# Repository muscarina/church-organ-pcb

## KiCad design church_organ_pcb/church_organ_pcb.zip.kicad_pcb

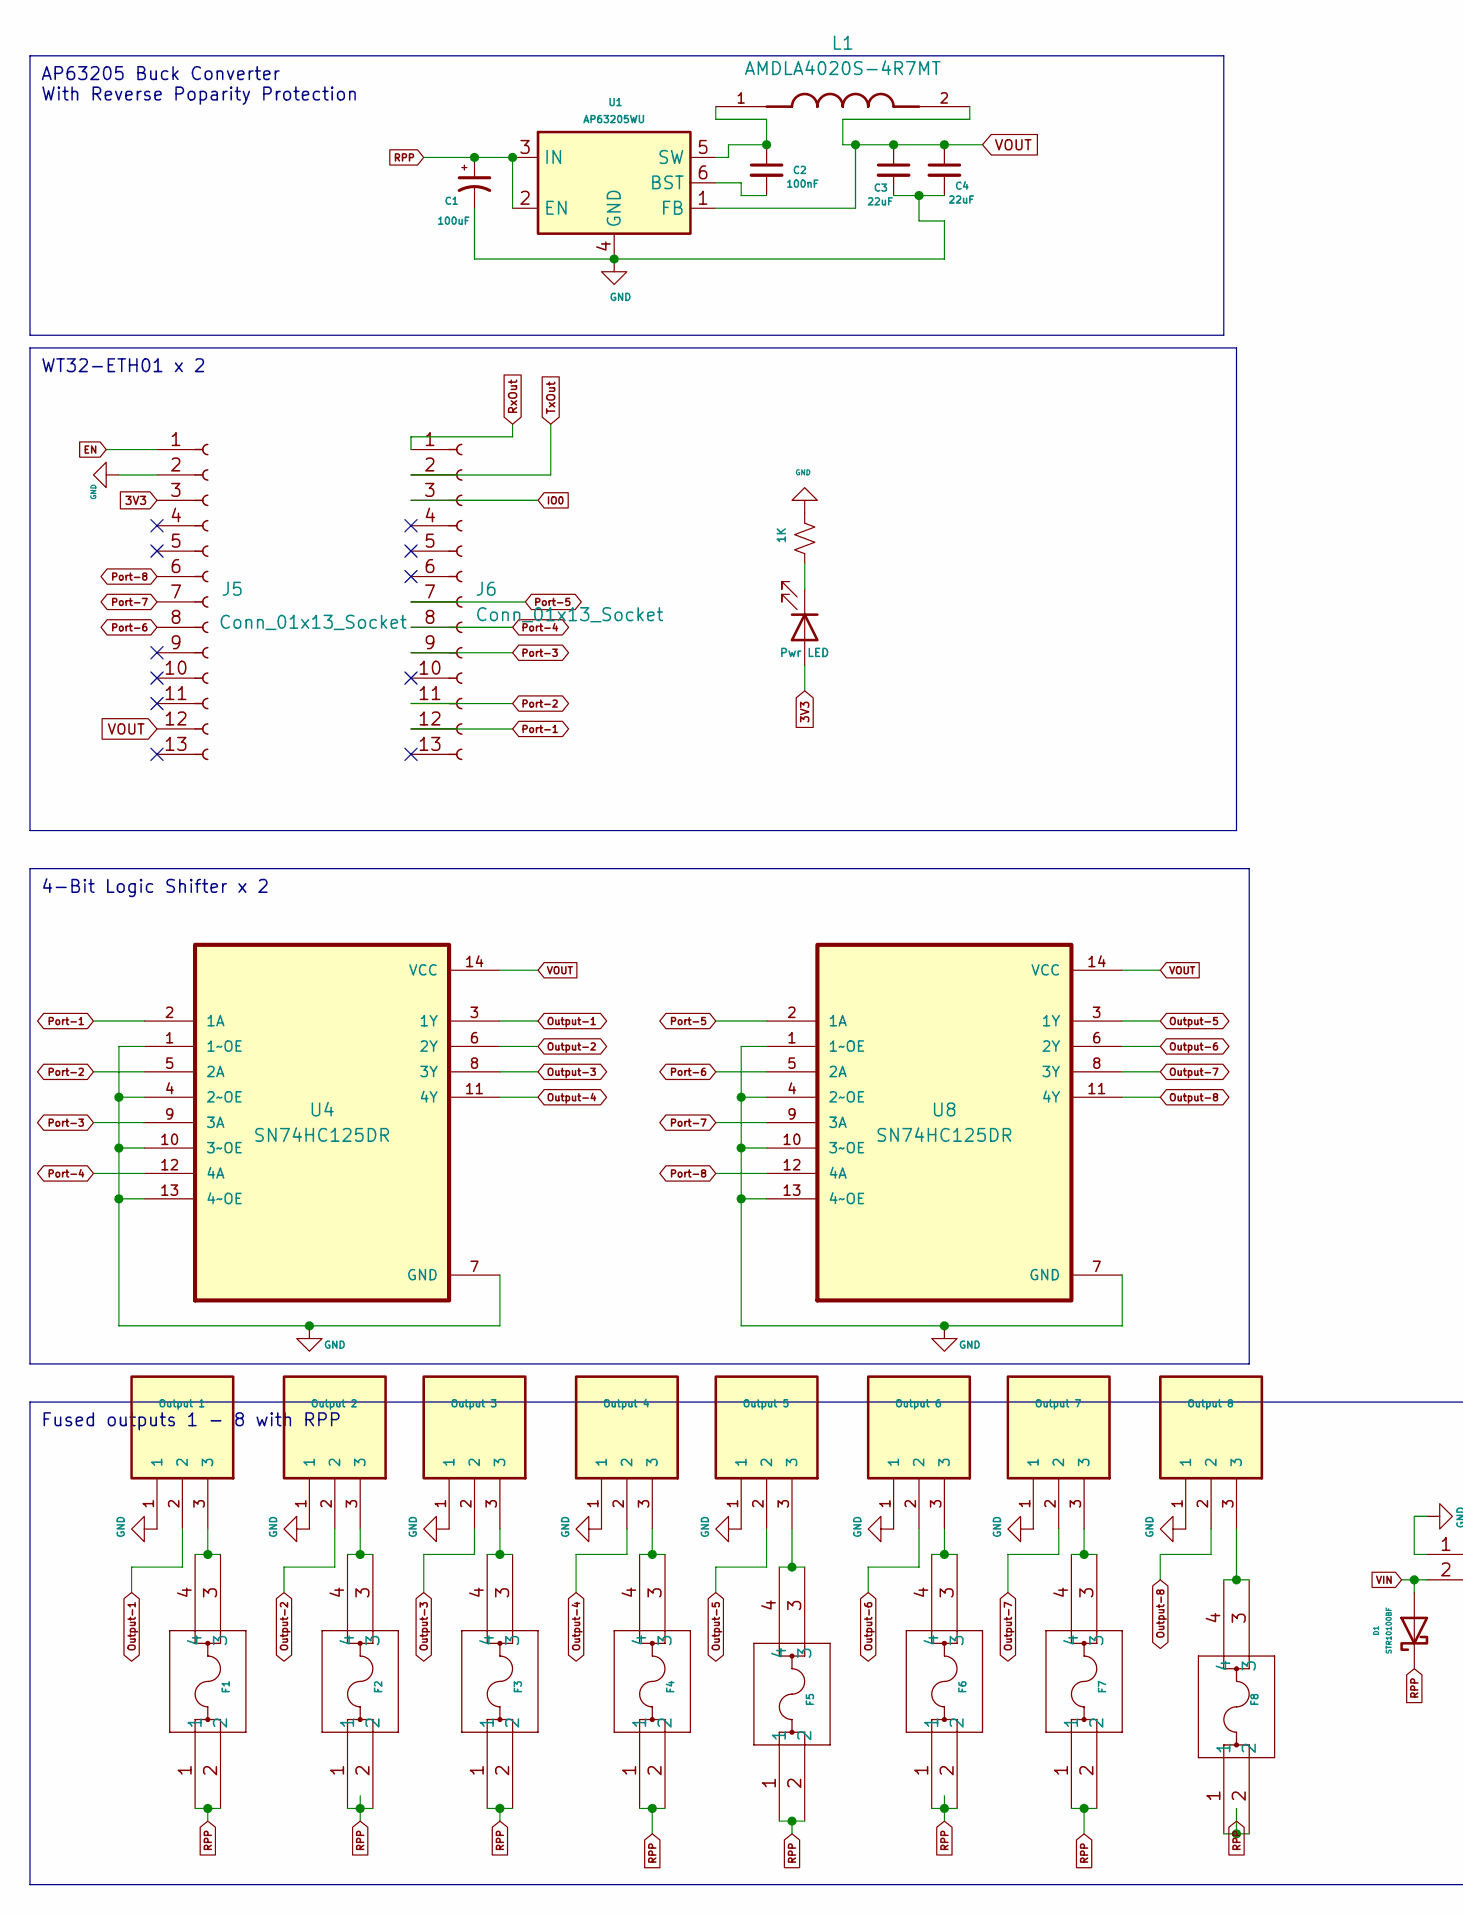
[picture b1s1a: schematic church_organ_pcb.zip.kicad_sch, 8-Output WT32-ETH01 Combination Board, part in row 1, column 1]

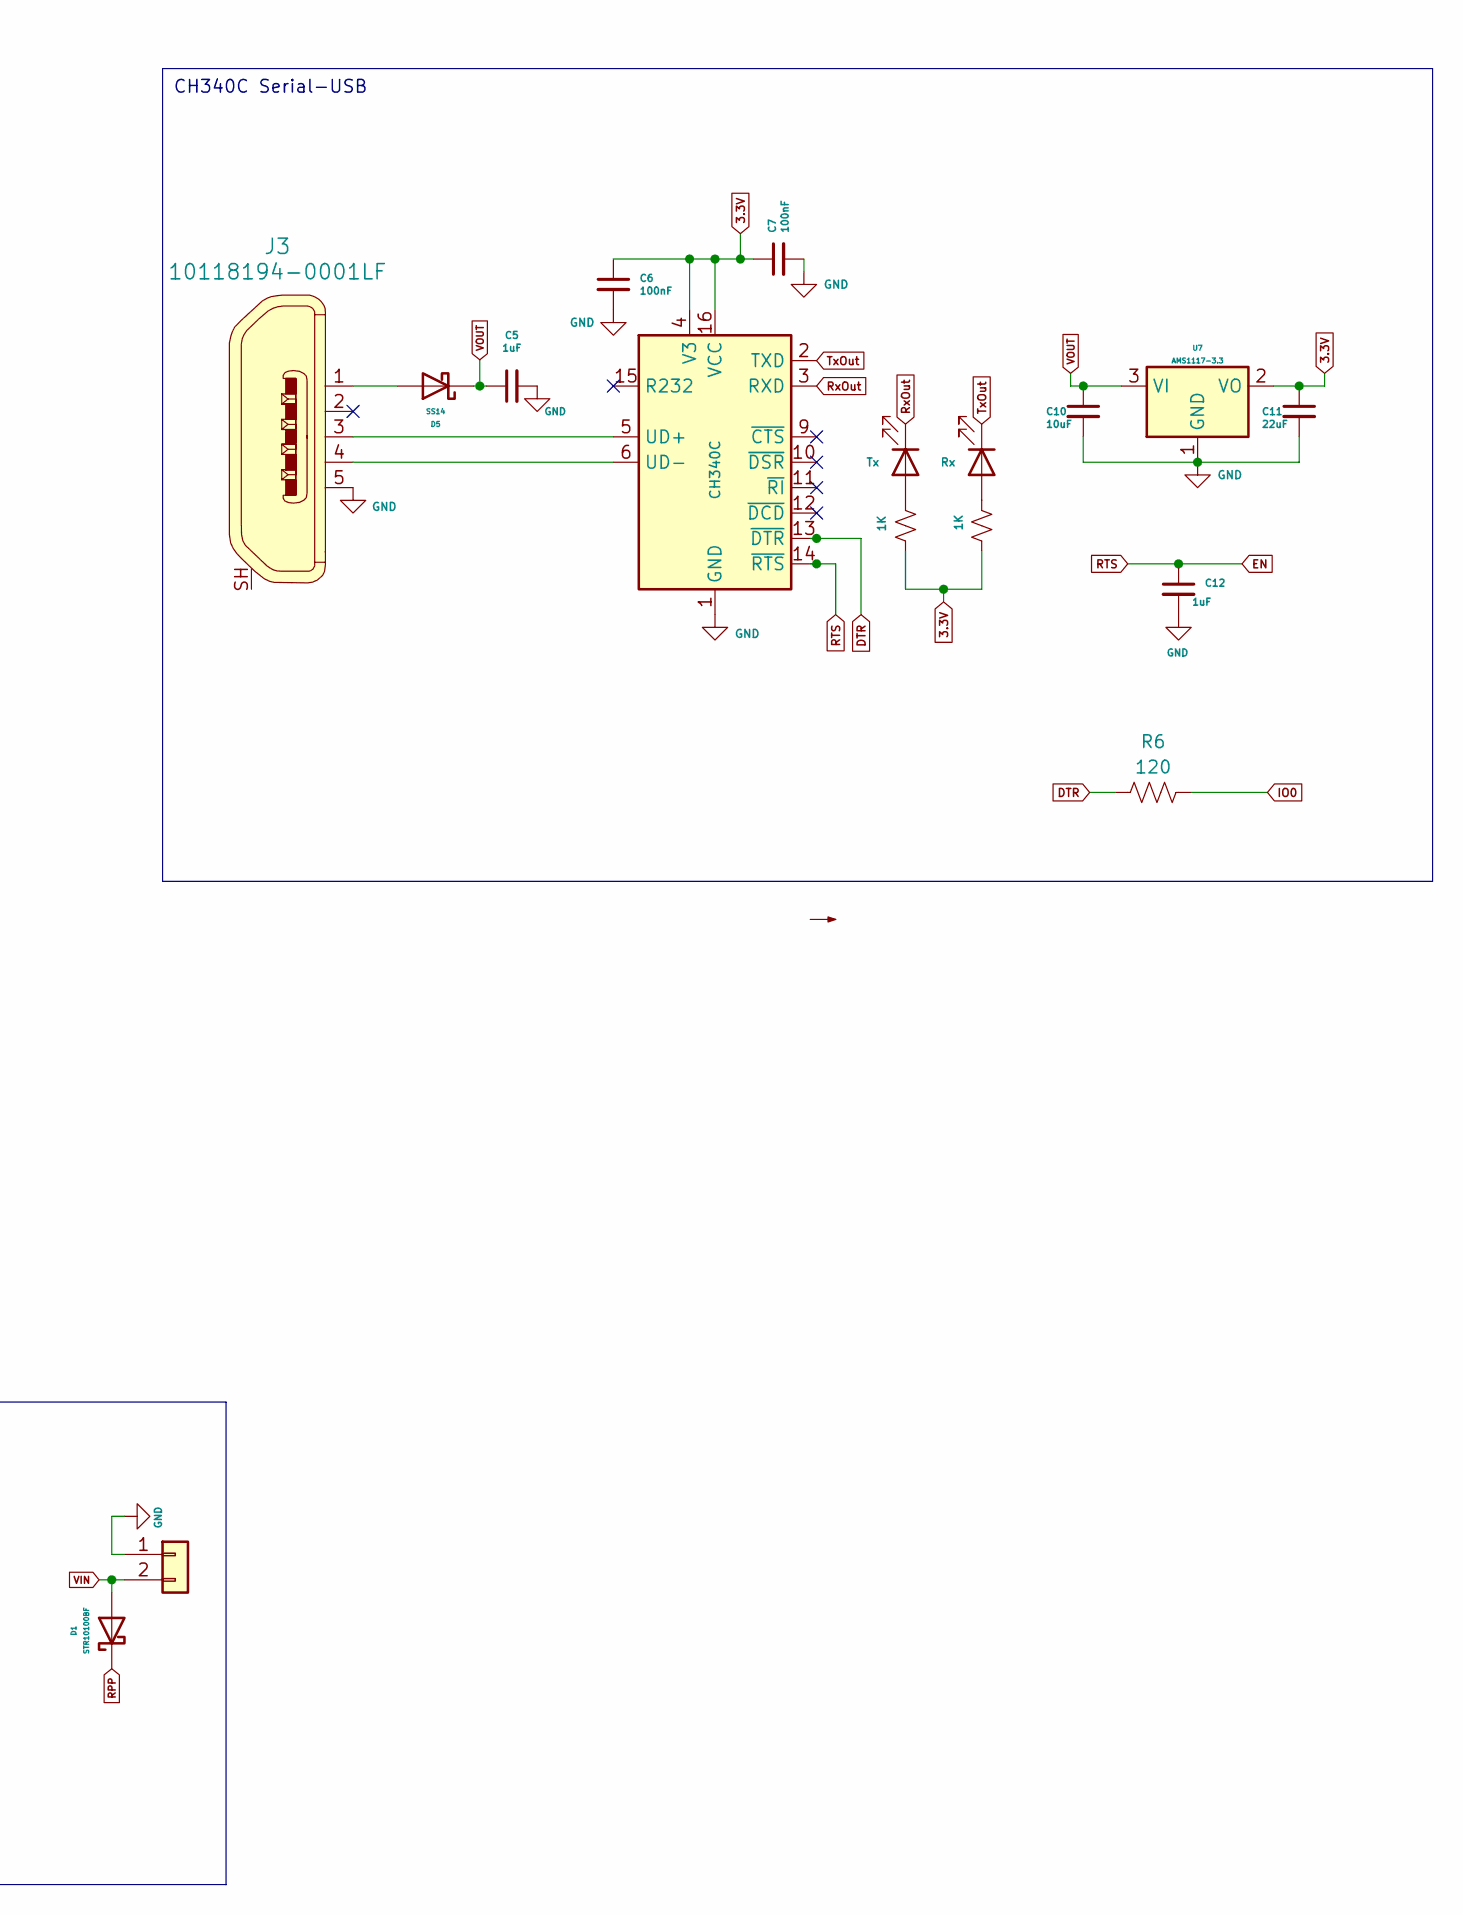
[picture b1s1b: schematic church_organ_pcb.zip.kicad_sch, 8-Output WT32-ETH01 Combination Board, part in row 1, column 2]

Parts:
C1: 100uF; CP_Elec_6.3x5.4
C2, C6, C7: 100nF; C_0805_2012Metric_Pad1.18x1.45mm_HandSolder
C3, C4, C11: 22uF; C_0805_2012Metric_Pad1.18x1.45mm_HandSolder
C5, C12: 1uF; C_0805_2012Metric_Pad1.18x1.45mm_HandSolder
C10: 10uF; C_0805_2012Metric_Pad1.18x1.45mm_HandSolder
D1: STR10100BF; D_SMB_Handsoldering
D2: Pwr LED; LED_0805_2012Metric_Pad1.15x1.40mm_HandSolder
D3: Tx; LED_0805_2012Metric_Pad1.15x1.40mm_HandSolder
D4: Rx; LED_0805_2012Metric_Pad1.15x1.40mm_HandSolder
D5: SS14; D_SOD-323_HandSoldering
F1, F2, F3, F4, F5, F6, F7, F8: CONN_3544-2_KEY
J1: 4.5-28V Power Input; CONN_691321300002_WRE
J3: 10118194-0001LF; USB_Micro_B_Female_10118194-0001LF; MPN 10118194-0001LF
J5, J6: Conn_01x13_Socket; PinSocket_1x13_P2.54mm_Vertical
JST1: Output 1; CUI_TBP02R2-381-03BE; Mfg Part# 1711738
JST2: Output 2; CUI_TBP02R2-381-03BE
JST3: Output 3; CUI_TBP02R2-381-03BE
JST4: Output 4; CUI_TBP02R2-381-03BE
JST5: Output 5; CUI_TBP02R2-381-03BE
JST6: Output 6; CUI_TBP02R2-381-03BE
JST7: Output 7; CUI_TBP02R2-381-03BE
JST8: Output 8; CUI_TBP02R2-381-03BE
L1: AMDLA4020S-4R7MT; IND_AMDLA4020S-4R7MT; PARTREV 9/16/2019
R1, R2, R3: 1K; R_0805_2012Metric_Pad1.20x1.40mm_HandSolder
R6: 120; R_0805_2012Metric_Pad1.20x1.40mm_HandSolder
U1: AP63205WU; TSOT-23-6
U4, U8: SN74HC125DR; SOIC127P600X175-14N
U5: CH340C; SOP-16_3.9x9.9mm_P1.27mm
U7: AMS1117-3.3; SOT-223-3_TabPin2

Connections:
3.3V: C6.1, C7.1, C11.1, R2.1, R3.2, U5.4 (V3), U5.16 (VCC), U7.2 (VO)
3V3: D2.2 (A), J5.3
DTR: R6.1, U5.13 (~DTR)
EN: C12.1, J5.1, U5.14 (~RTS)
GND: C1.2, C3.2, C4.2, C5.2, C6.2, C7.2, C10.2, C11.2, C12.2, J1.1, J3.5, J5.2, JST1.1, JST2.1, JST3.1, JST4.1, JST5.1, JST6.1, JST7.1, JST8.1, R1.1, U1.4 (GND), U4.1 (1~OE), U4.4 (2~OE), U4.7 (GND), U4.10 (3~OE), U4.13 (4~OE), U5.1 (GND), U7.1 (GND), U8.1 (1~OE), U8.4 (2~OE), U8.7 (GND), U8.10 (3~OE), U8.13 (4~OE)
IO0: J6.3, R6.2
unnamed: D2.1 (K), R1.2
unnamed: D3.2 (A), R2.2
unnamed: D4.2 (A), R3.1
unnamed: D5.2 (A), J3.1
unnamed: F1.3, F1.4, JST1.3
unnamed: F2.3, F2.4, JST2.3
unnamed: F3.3, F3.4, JST3.3
unnamed: F4.3, F4.4, JST4.3
unnamed: F5.3, F5.4, JST5.3
unnamed: F6.3, F6.4, JST6.3
unnamed: F7.3, F7.4, JST7.3
unnamed: F8.3, F8.4, JST8.3
unnamed: C2.2, U1.6 (BST)
unnamed: C2.1, L1.1, U1.5 (SW)
unnamed: J3.3, U5.5 (UD+)
unnamed: J3.4, U5.6 (UD-)
Output-1: JST1.2, U4.3 (1Y)
Output-2: JST2.2, U4.6 (2Y)
Output-3: JST3.2, U4.8 (3Y)
Output-4: JST4.2, U4.11 (4Y)
Output-5: JST5.2, U8.3 (1Y)
Output-6: JST6.2, U8.6 (2Y)
Output-7: JST7.2, U8.8 (3Y)
Output-8: JST8.2, U8.11 (4Y)
Port-1: J6.12, U4.2 (1A)
Port-2: J6.11, U4.5 (2A)
Port-3: J6.9, U4.9 (3A)
Port-4: J6.8, U4.12 (4A)
Port-5: J6.7, U8.2 (1A)
Port-6: J5.8, U8.5 (2A)
Port-7: J5.7, U8.9 (3A)
Port-8: J5.6, U8.12 (4A)
RPP: C1.1, D1.1 (K), F1.1, F1.2, F2.1, F2.2, F3.1, F3.2, F4.1, F4.2, F5.1, F5.2, F6.1, F6.2, F7.1, F7.2, F8.1, F8.2, U1.2 (EN), U1.3 (IN)
RxOut: D3.1 (K), J6.1, U5.3 (RXD)
TxOut: D4.1 (K), J6.2, U5.2 (TXD)
VIN: D1.2 (A), J1.2
VOUT: C3.1, C4.1, C5.1, C10.1, D5.1 (K), J5.12, L1.2, U1.1 (FB), U4.14 (VCC), U7.3 (VI), U8.14 (VCC)

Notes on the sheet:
AP63205 Buck Converter With Reverse Poparity Protection
4-Bit Logic Shifter x 2
CH340C Serial-USB
WT32-ETH01 x 2
Fused outputs 1 - 8 with RPP

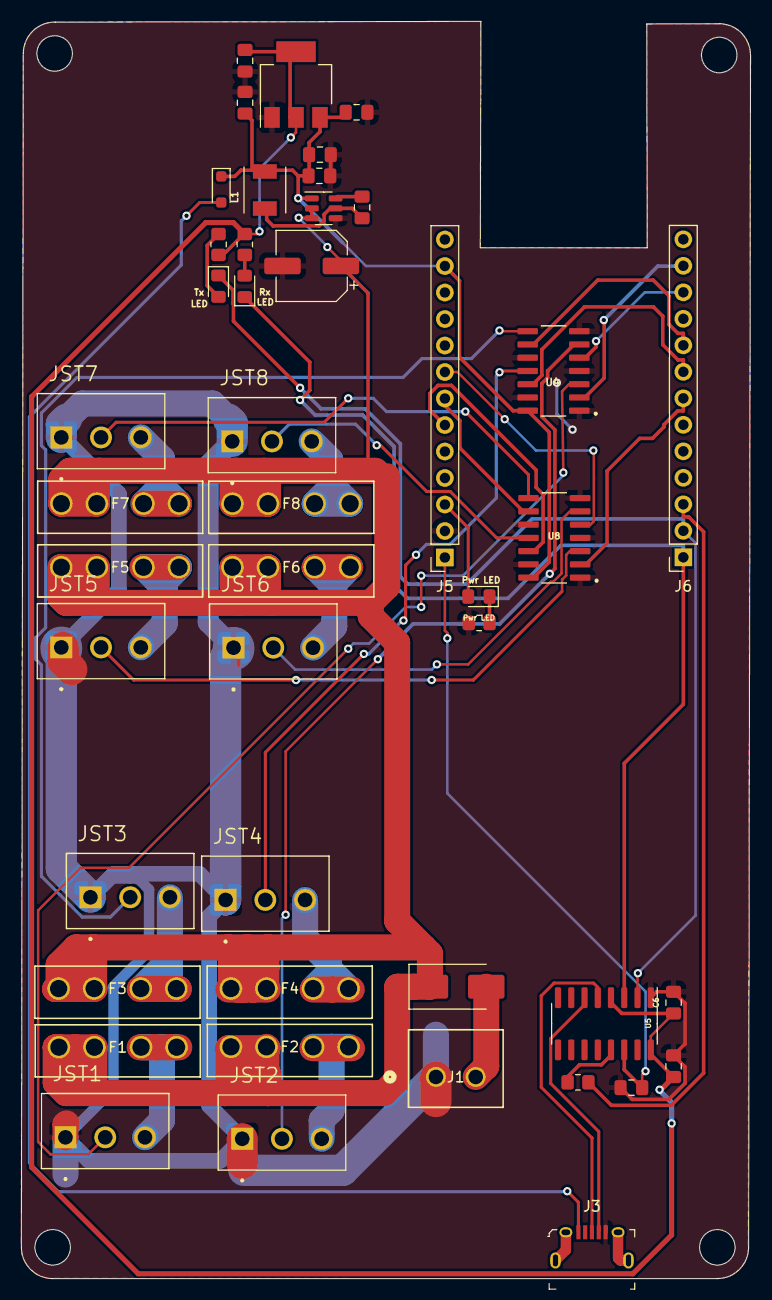
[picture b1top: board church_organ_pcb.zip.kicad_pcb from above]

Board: 2 copper layers, 69.9 x 120.5 mm, 45 parts (0 on the bottom side), 43 nets.

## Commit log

2024-05-21 komponentfootprints tillagda
2024-05-25 removed fan outputs and regulator, fixed traces and removed esp32s, made holes bigger for screws
2024-05-25 schema edited
2024-06-02 Remove old files
2024-06-02 Add new components
2024-06-02 Moved "komponenter" folder
2024-06-02 Add new project libs of components
    Using project placeholder substituion variable
2024-06-02 Commit autosave files
2024-06-02 Commit changes to PCB
    Rerouted power traces to/from the fuses
    Replaced screw terminal with quick connect terminals
    Fixed an issue where LED-outputs 5,6,7,8 was not correctly connected to their NETs
2024-06-02 rerouted most of board
2024-06-02 Fixed scattered groundplane
2024-06-04 Added inductor to komponenter folder
2024-06-05 Add new 4.7mH inductor to voltage regulator circuit + fix 3d models
